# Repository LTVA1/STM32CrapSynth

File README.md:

# STM32CrapSynth

A software/hardware synth based on STM32F303RE, 4xAD9833 wave generators, one MM5437 noise generator and LTC1063 lowpass filter. Currently I seem to have burned the filter so instead there's 3rd PCM channel using the timer that was planned for filter clocking.

# Music demo

[Here's the demo](https://www.youtube.com/watch?v=L5HF_qdjZyU). I recorded each channel separately for channel oscilloscopes and then recorded them all for master sound which you can hear in the video.

# Folders

`board` - KiCAD project of the board that mounts on top of custom teacher's board like Arduino shield.
`pc_program` - small CLI program using serial library to send data to the MCU. There also lies `.fur` tracker module of the soundtrack (but remember that emulation is finished and it sounds off at times compared to real hardware)
`STM32CrapSynthFirmware` - MCU firmware written only with CMSIS register defs and simple functions. Zero HAL, LL, SPL libraries usage.

# Other programs

[STM32CrapSynth in Furnace](https://github.com/LTVA1/furnace/tree/stm32crapsynth) - A fork of Furnace chiptune tracker with added emulation of STM32CrapSynth. Also has an ability to export data (samples and stream of commands/wavetable data) into the file which is then used by `pc_program`.

# Overview and explanation

The device is capable of synthesizing 8 audio channels. Their signals are added together and the resulting sum is available on standard 3.5 mm audio jack.

There also are six phase reset timers. Two of them are MCU's internal timers and four other are four MCU's internal USARTs/UARTs which were made to generate a periodic interrupt (just like the usual timers). Each timer has 8-bit bitmask dictating which channels it affects. Each time timer fires the correspodning channel's signal phase is reset.

The device consists of three PCBs. I designed only the topmost PCB with `STM32CrapSynth` logo. Lower two PCBs were designed by my teacher.

Here is the overall image of the whole device.

## Top PCB

Muxes are used to connect either MCU timer's PWM signal or AD9833 signal to the attenuator's input. Four channels are formed, each having the ability to play sound from its own PWM timer or from its own AD9833 waveform generator.

Attenuators allow to control the channel's volume with 0.5dB step.

Noise generator can either be clocked from its own internal oscillator or from external signal (the latter is generated by dedicated MCU timer in PWM generation mode). With external clock and another control signal it's also possible to load LFSR directly from MCU, which allows to reset the noise generation at any time. That's how it is possible to "phase reset" noise channel.

The rightmost attenuator controls signals that come from brown wires. These are soldered to the outputs on MCU board that act as MCU's internal DACs outputs.

Eighth channel emerges from PWM signal that comes directly from MCU pin. Since op-amp isn't designed to handle such high frequencies, the form of the signal from this channel is distorted as you can see in demo video (triangle wave is "smoothed" on one side).

Wires were soldered to an external wires-to-audio-jack adapter because, when designing a PCB, I used wrong audio jack footprint.

External Flash memory holds a dump of commands. These commands control frequency, volume and other settings of each audio channel. They also specify the rate of their execution. Each time the timer fires (240 times a second in demo video) command execution happens until a special command is encountered. The special command stops any further execution until the timer fires next time.

## Middle PCB

On the other side on top PCB there are capacitors for power noise elimination and two more AD9833 boards.

On middle PCB you can see the main MCU that performs all the work and USB-UART bridge. The data transfer rate is 2MBaud. Also the places where DAC signal wires are soldered are visible.

## Bottom PCB

Nothing special here, just a small PCB with custom STLink debugger design. A connector between bottom and middle PCB is visible on top. The USB connector provides power to STLink.

Also this board has 3.3V power regulator that supplies main MCU and external Flash memory.

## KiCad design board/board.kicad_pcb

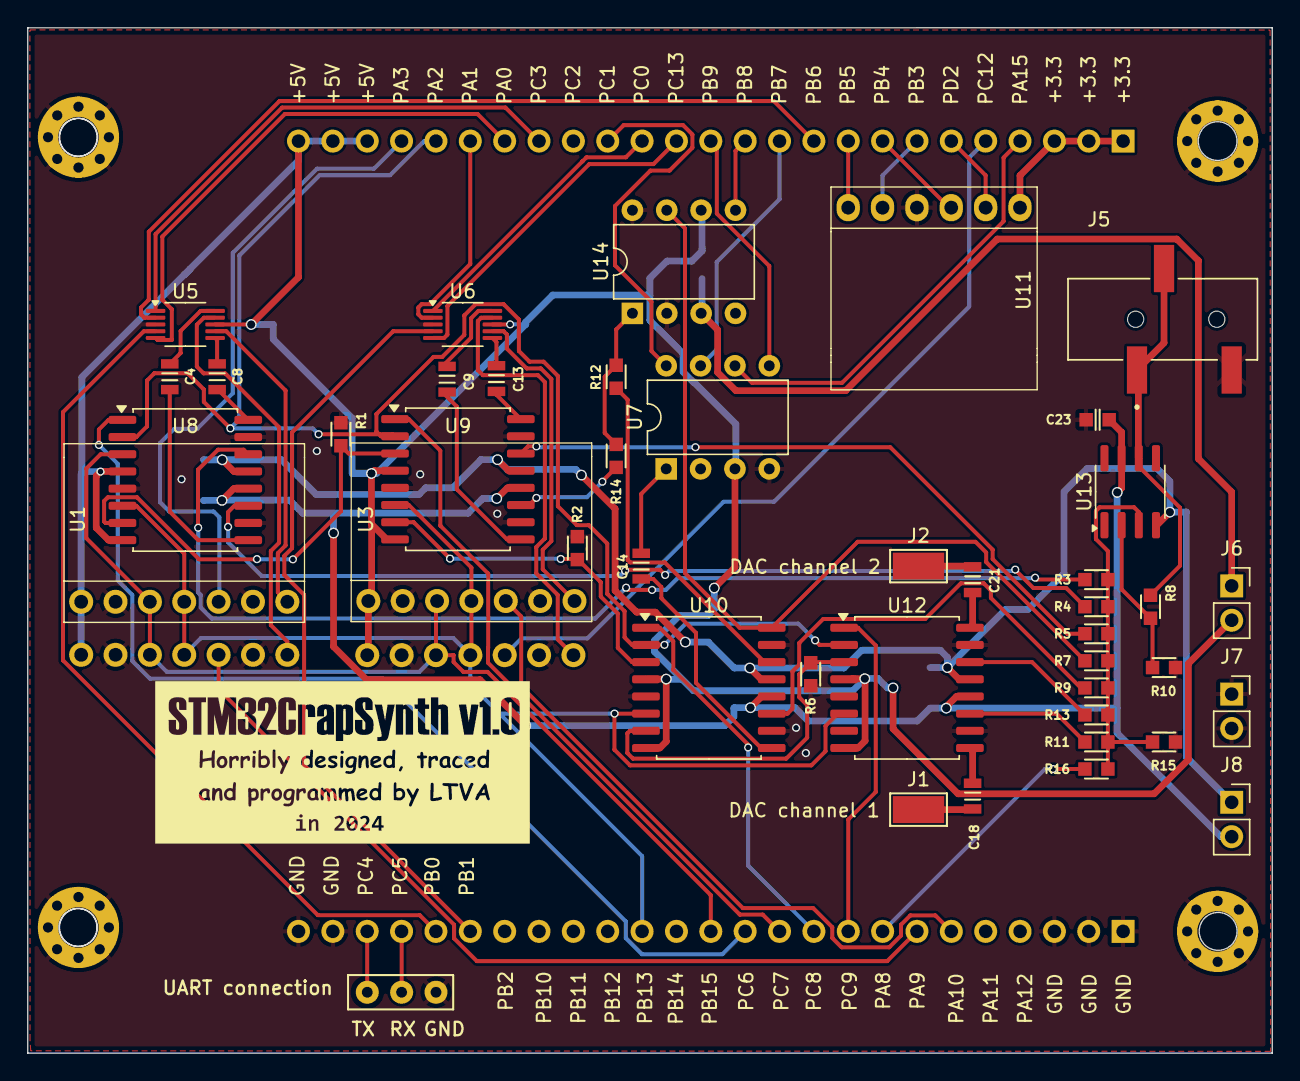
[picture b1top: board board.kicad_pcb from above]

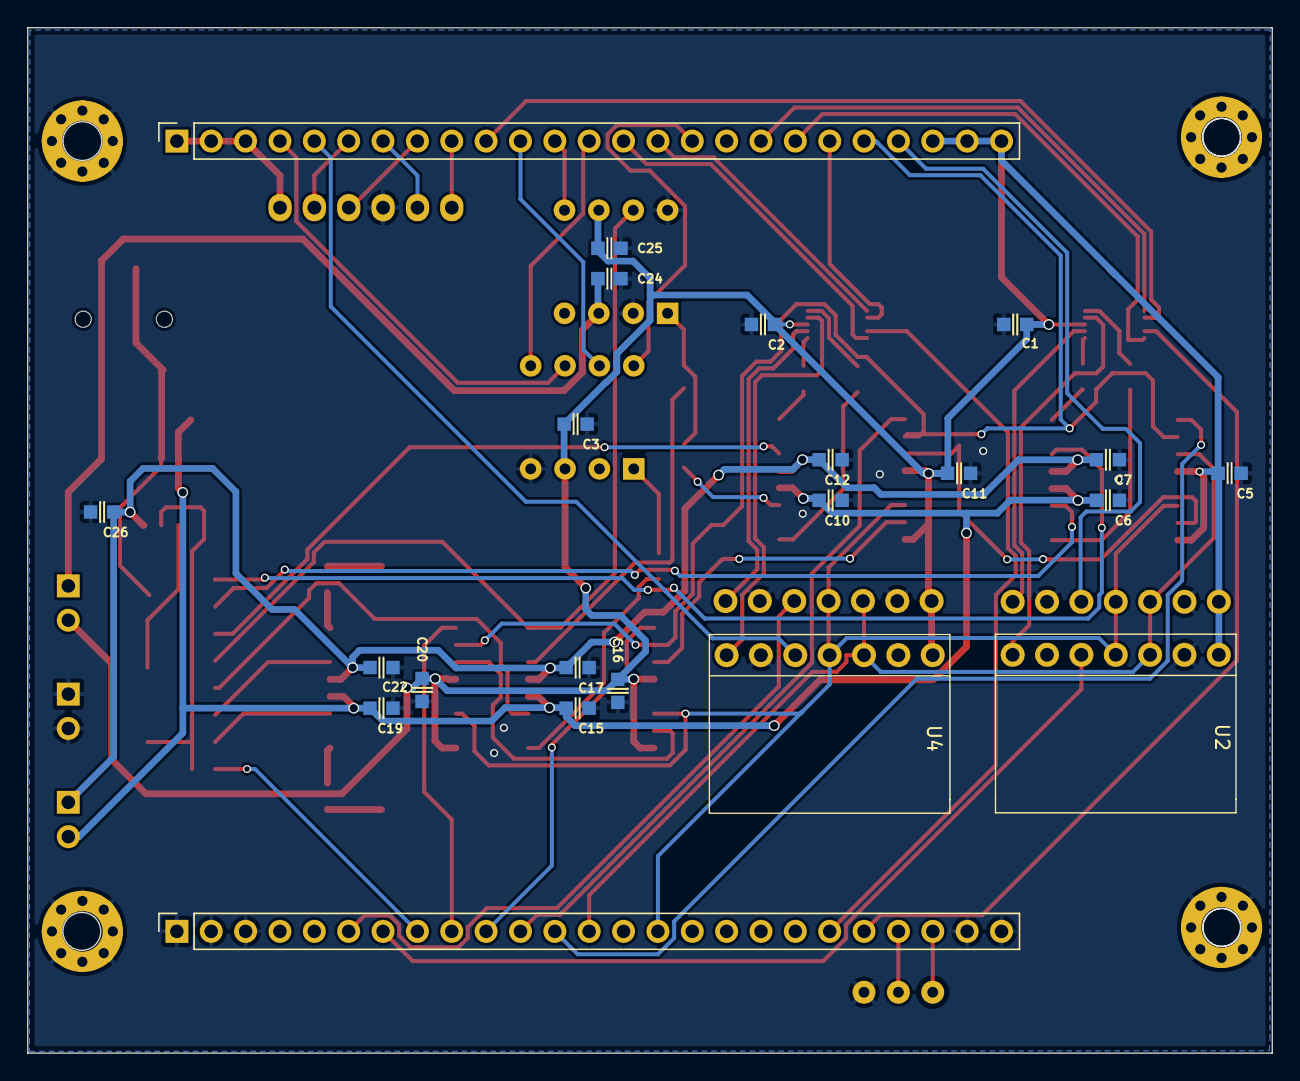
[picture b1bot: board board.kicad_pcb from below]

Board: 2 copper layers, 92.0 x 75.8 mm, 69 parts (23 on the bottom side), 71 nets.

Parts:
C1, C2, C3, C5, C6, C7, C10, C11, C12, C15, C16, C17, C19, C20, C22, C23, C24, C25, C26: 0.22uF_0603_25V; C_0603
C4, C8, C9, C13, C14, C18, C21: 22uF_0603_16V; C_0805
J1, J2: TestPoint_Keystone_5019_Minature
J2#2, J3, J4, J5#2: Conn_01x01; M3
J3#2, J4#2: Conn_01x25_Socket; PinSocket_1x25_P2.54mm_Vertical
J5: PJ-320B; BOOMELE_PJ-320B
J6, J7, J8: Screw_Terminal_01x02; Socket_1x02_2.54mm_TH
J9: UART_port
R1, R2, R6: 100k_0603; R_0603
R3, R4, R5, R7, R9, R11, R13, R16: 3.0k_0603_0.1%; R_0603
R8: 2.2k_0603; R_0603
R10, R12, R14, R15: 1k_0603_0.1%; R_0603
U1, U2, U3, U4: AD9833
U5, U6: VSSOP-10_3x3mm_P0.5mm
U7, U14: DIP-8pin_TH
U8, U9, U10, U12: SOIC-16W_7.5x10.3mm_P1.27mm
U11: W25Q128_board
U13: SOIC-8_3.9x4.9mm_P1.27mm

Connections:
+3.3V: J4#2.1, J4#2.2, J4#2.3, U11.1 (VDD)
+5V: C1.1, C2.1, C3.1, C5.1, C11.1, C16.1, C20.1, C25.1, J4#2.23, J4#2.24, J4#2.25, J6.2, U1.1 (Vcc), U2.1 (Vcc), U3.1 (Vcc), U4.1 (Vcc), U5.8 (Vdd), U6.8 (Vdd), U7.3 (Vdd), U8.4 (VD+), U8.8 (/MUTE), U9.4 (VD+), U9.8 (/MUTE), U10.4 (VD+), U10.8 (/MUTE), U12.4 (VD+), U12.8 (/MUTE), U14.6 (V+)
ATTEN_CS: J4#2.21, U8.2 (/CS), U9.2 (/CS), U10.2 (/CS), U12.2 (/CS)
Analog_CLK: J3#2.15, U1.4 (SCLK), U2.4 (SCLK), U3.4 (SCLK), U4.4 (SCLK), U8.6 (SCLK), U9.6 (SCLK), U10.6 (SCLK), U12.6 (SCLK)
Analog_data: J3#2.13, U1.3 (SDATA), U2.3 (SDATA), U3.3 (SDATA), U4.3 (SDATA), U8.3 (SDI)
Analog_data_out1: R1.2, U8.7 (SDO), U9.3 (SDI)
Analog_data_out2: R2.2, U9.7 (SDO), U10.3 (SDI)
Analog_data_out3: R6.2, U10.7 (SDO), U12.3 (SDI)
CH1_OUT: R3.1, U8.14 (VoutL)
CH1_TOVOL: C8.2, U5.6 (D2)
CH2_OUT: R4.1, U8.11 (VoutR)
CH2_TOVOL: C4.2, U5.10 (D1)
CH3_OUT: R5.1, U9.14 (VoutL)
CH3_TOVOL: C13.2, U6.6 (D2)
CH4_OUT: R7.1, U10.16 (VinL), U14.7 (Vout)
CH4_TOFILT: R14.2, U9.11 (VoutR)
CH4_TOVOL: C9.2, U6.10 (D1)
CS_AD9833_1: J4#2.22, U1.5 (FSYNC)
CS_AD9833_2: J3#2.7, U2.5 (FSYNC)
CS_AD9833_3: J3#2.6, U3.5 (FSYNC)
CS_AD9833_4: J4#2.5, U4.5 (FSYNC)
DAC_out1: R11.1, U12.11 (VoutR)
DAC_out2: R13.1, U12.14 (VoutL)
DAC_tovol1: C18.2, J1.1 (Input)
DAC_tovol2: C21.2, J2.1 (Input)
DDS1_out: U1.7 (OUT), U5.7 (S2B)
DDS2_out: U2.7 (OUT), U5.9 (S1B)
DDS3_out: U3.7 (OUT), U6.7 (S2B)
DDS4_out: U4.7 (OUT), U6.9 (S1B)
FILTER_FEEDBACK_OUT: R12.1, U10.14 (VoutL)
FILT_CLK: J4#2.12, U14.5 (CLK_IN)
FLASH_CLK: J4#2.7, U11.5 (SCLK)
FLASH_CS: J4#2.6, U11.2 (/CS)
FLASH_MISO: J4#2.8, U11.3 (DO)
FLASH_MOSI: J4#2.9, U11.6 (DI)
GND: C1.2, C2.2, C3.2, C5.2, C6.2, C7.2, C10.2, C11.2, C12.2, C15.2, C16.2, C17.2, C19.2, C20.2, C22.2, C23.2, C24.2, C25.2, C26.2, J2#2.1, J3.1, J3#2.1, J3#2.2, J3#2.3, J3#2.24, J3#2.25, J4.1, J5.3, J5#2.1, J7.1, J7.2, J9.3 (GND), R1.1, R2.1, R6.1, R10.2, R15.2, U1.2 (DGND), U1.6 (AGND), U2.2 (DGND), U2.6 (AGND), U3.2 (DGND), U3.6 (AGND), U4.2 (DGND), U4.6 (AGND), U5.3 (GND), U6.3 (GND), U7.4 (Vss), U8.5 (DGND), U8.10 (AGNDR), U8.15 (AGNDL), U9.5 (DGND), U9.10 (AGNDR), U9.15 (AGNDL), U10.5 (DGND), U10.10 (AGNDR), U10.15 (AGNDL), U11.4 (GND), U12.5 (DGND), U12.10 (AGNDR), U12.15 (AGNDL), U14.2 (GND), U14.8 (Vos_ADJ)
MUX_SEL_1: J4#2.18, U5.1 (SEL1)
MUX_SEL_2: J4#2.19, U5.5 (SEL2)
MUX_SEL_3: J4#2.14, U6.5 (SEL2)
MUX_SEL_4: J4#2.15, U6.1 (SEL1)
NOISE_CLK: J4#2.11, U7.7 (CLK)
NOISE_CLK_SEL: J4#2.16, U7.8 (/CONTROL1)
NOISE_CS: J4#2.4, U7.6 (/CONTROL2)
NOISE_DI: J4#2.13, U7.5 (OUT_2/DATA_IN)
NOISE_OUT: R9.1, U10.11 (VoutR)
NOISE_TOVOL: C14.2, U7.1 (OUT)
unnamed: C8.1, U8.16 (VinL)
unnamed: C4.1, U8.9 (VinR)
unnamed: C13.1, U9.16 (VinL)
unnamed: C9.1, U9.9 (VinR)
unnamed: C14.1, U10.9 (VinR)
unnamed: C21.1, U12.16 (VinL)
unnamed: C18.1, U12.9 (VinR)
unnamed: R3.2, R4.2, R5.2, R7.2, R9.2, R11.2, R13.2, R15.1, R16.2, U13.3 (In+)
unnamed: R8.2, R10.1, U13.2 (In-)
unnamed: J5.1, J5.2, R8.1, U13.6 (Output)
unnamed: R12.2, R14.1, U14.1 (Vin)
P,+15: C6.1, C10.1, C15.1, C19.1, C23.1, J8.2, U8.12 (Va+), U9.12 (Va+), U10.12 (Va+), U12.12 (Va+), U13.7 (V+)
P,-5: C24.1, J6.1, U14.3 (V-)
P,-15: C7.1, C12.1, C17.1, C22.1, C26.1, J8.1, U8.13 (Va-), U9.13 (Va-), U10.13 (Va-), U12.13 (Va-), U13.4 (V-)
PWM1: J3#2.21, U5.4 (S2A)
PWM2: J4#2.10, U5.2 (S1A)
PWM3: J3#2.20, U6.4 (S2A)
PWM4: J4#2.20, U6.2 (S1A)
PWM_DAC_out: J3#2.8, R16.1
UART_RX: J3#2.22, J9.2 (RX)
UART_TX: J3#2.23, J9.1 (TX)
ZCEN_1: J3#2.12, U8.1 (ZCEN)
ZCEN_2: J3#2.11, U9.1 (ZCEN)
ZCEN_3: J3#2.10, U10.1 (ZCEN)
ZCEN_DAC: J3#2.9, U12.1 (ZCEN)

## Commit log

2024-09-24 connection successful message + add resistor to filter feedback loop
2024-09-24 cleanup...
2024-09-24 add noise clock source and mute function control
2024-09-25 fuck it, I ordered 4 2-ch attenuators so let there be DAC volume control!
2024-09-25 free uart pins
2024-09-27 added 1 more resistor to filter feedback, added +5v to remaining screw terminal, connected L & R audio channels for 3.5 mm jack
2024-09-28 reassign noise pins so that noise clock and noise data in are on the same GPIO port
2024-09-30 placed components
2024-09-30 add Ux reference to boards and place components again...
2024-09-30 horrible attempt at placing components
2024-09-30 add caps on power lines, start tracing
2024-09-30 traced (changed some CS and mux select pins to make tracing easier)
    Dude that's horrible PCB...
2024-09-30 optimize board or idk
2024-09-30 temporary gerbers
2024-10-01 attempt at tracing v2
2024-10-01 W I D E
2024-10-01 more tracing...
2024-10-01 more tracing tweaks
2024-10-02 start writing MCU firmware
2024-10-02 Correct wrong amount of CCM RAM in linker script
2024-10-02 unlock flash function
2024-10-02 freeze timers in debug...
2024-10-03 new opamp, timers init
2024-10-05 more board rework, UART & SPI init
2024-10-08 DAC init
2024-10-09 add РПЗ template
2024-10-09 added DMA init
2024-10-10 finish functional schematic?
2024-10-10 -Os compilation flag, add one more DMA channel for noise chip LFSR load
2024-10-11 add test file, add template data loading through UART
2024-10-11 uncomment timer init
2024-10-12 dummy response packets reading & checking data integrity, added long test file
2024-10-12 added separate connector for UART
2024-10-12 write external Flash reset commands and request ID, init GPIO, done with initial comms establishment packet
2024-10-13 added UART commands decode and internal flash erase and write functions, wrote down state
2024-10-14 external flash: writing data and erasing sectors
2024-10-15 add clocks enable for ADCs and UART4, change course project theme
    May later be used as timers
2024-10-16 add AD9833 communication functions
2024-10-16 PGA2320 driver, send only relative packet address, implement actual "task" to write into external flash, send response packet after writing data,
    Also in pc program send only relative data address (without flash or RAM array start offset)
2024-10-26 fix uart comms, place interrupt handlers in ccmram, AD9833 works
2024-10-26 place interrupt vector table to CCMRAM
2024-10-26 DAC works via DAM for wavetables
2024-10-26 spi is 4 bytes late on receive due to FIFO...
    also test wavetable working with DAC
2024-10-27 spi flash works! read-erase-write
2024-10-27 external flash multiple pages write with proper sector erase, internal flash write
2024-10-27 fix sending external Flash chip UID
2024-10-27 test both DAC channels with tri and noise gen
    2nd channel saturates at around 90% voltage, why?...
2024-10-27 play samples from internal flash, longer than 65535 steps, with custom loop point
2024-10-28 return this
2024-11-01 hopefully final PCB
2024-11-03 crapsynth works with dac channels lmao
2024-11-03 a couple of fixes
2024-11-03 skip nops more efficiently
2024-11-04 make DMA-copying wavetables work
2024-11-04 last minute addition (PWM DAC lmao), gerber files,
2024-11-06 fix wavetable jerk
2024-11-09 fix wavtebles reading via DMA, now you can pad waves at 8k pages instead of 4k, thus file/data size is reduced
2024-11-10 FPGA noise generator implementation, now just LFSR with fixed clock
2024-11-10 Try to code FPGA SPI differently (still doesn't want to compile and work)
2024-11-10 IT WORKS!
2024-11-11 make separate commands to reset LFSR and change frequency, make command size 3 bytes
2024-11-22 attenuators work, DDS works again, DDS/PWM switch works, tested on real board which I finally soldered together
2024-11-23 Remove RTC, make all channels work on real device except 4th DDS/PWM (needs a wire to be soldered) and phase reset timers
2024-11-24 Bigger data blocks, 2MBauds, phase reset timers commands
    Only two timers and 1 USART work as phase reset timers properly... others do some weird shit
2024-11-24 still doesn't work
2024-11-29 a version that kinda works?
2024-12-03 lmao why I deleted all this. Anyway return some files, clean up the code, hopefully final version of the report etc.
    Also add potential muting ability to the PWM DAC chan
2024-12-04 phase reset for PWM too
2024-12-06 damn fix duty
2024-12-06 awful hack to make samples play properly
2024-12-11 fix wave reset
2024-12-13 fix resetting uart timers
2024-12-15 hopefully final version
2024-12-21 add pictures
2024-12-21 oops
2025-05-24 add module
